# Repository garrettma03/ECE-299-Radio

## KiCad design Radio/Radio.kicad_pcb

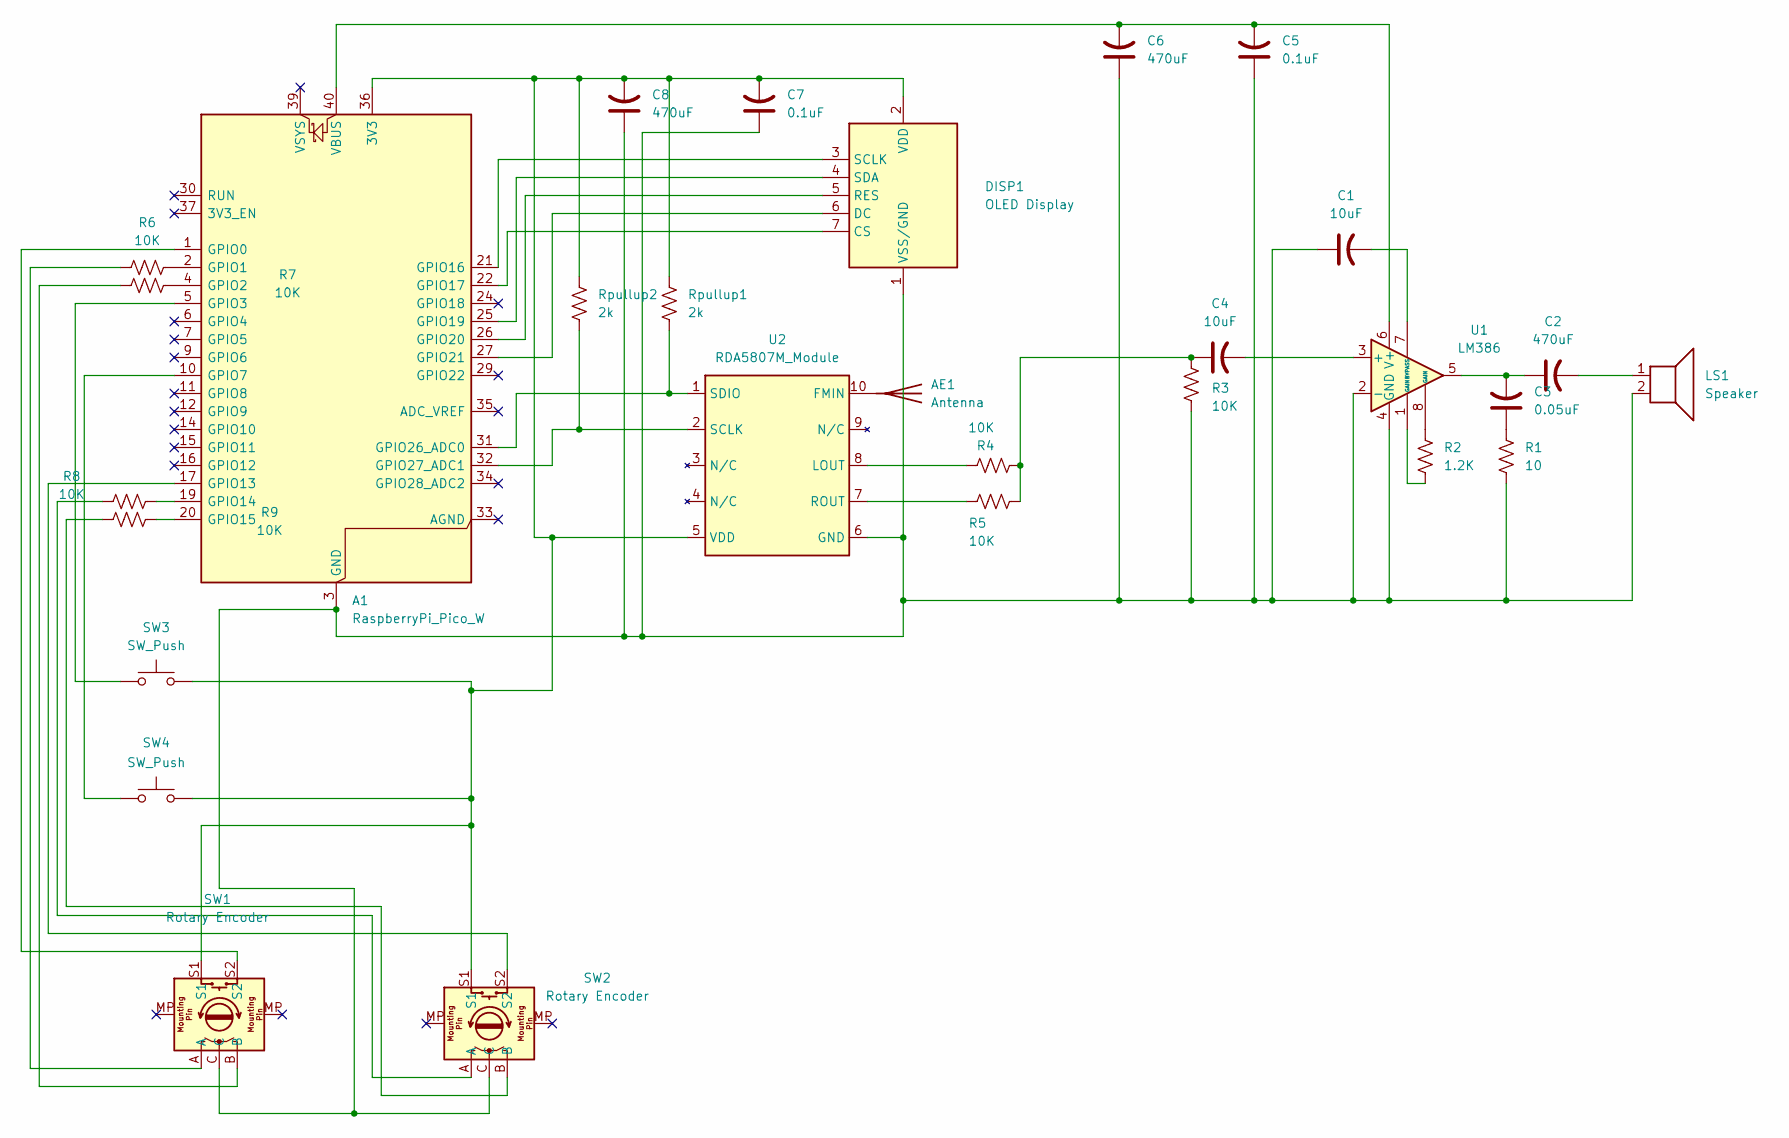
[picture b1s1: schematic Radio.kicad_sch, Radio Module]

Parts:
A1: RaspberryPi_Pico_W; RPi_Pico_TH
AE1: Antenna; TestPoint_Pad_D1.0mm
C1, C4: 10uF; CP_Radial_D6.3mm_P2.50mm
C2, C6, C8: 470uF; CP_Radial_D6.3mm_P2.50mm
C3: 0.05uF; C_Disc_D3.0mm_W1.6mm_P2.50mm
C5, C7: 0.1uF; C_Disc_D3.0mm_W1.6mm_P2.50mm
DISP1: OLED Display; OLED_Display_1.3
LS1: Speaker; TerminalBlock_Phoenix_MKDS-1,5-2_1x02_P5.00mm_Horizontal
R1: 10; R_Axial_DIN0207_L6.3mm_D2.5mm_P10.16mm_Horizontal
R2: 1.2K; R_Axial_DIN0207_L6.3mm_D2.5mm_P10.16mm_Horizontal
R3, R4, R5, R6, R7, R8, R9: 10K; R_Axial_DIN0207_L6.3mm_D2.5mm_P10.16mm_Horizontal
Rpullup1, Rpullup2: 2k; R_Axial_DIN0207_L6.3mm_D2.5mm_P10.16mm_Horizontal
SW1, SW2: Rotary Encoder; RotaryEncoder_Alps_EC12E-Switch_Vertical_H20mm
SW3, SW4: SW_Push; SW_PUSH_6mm
U1: LM386; DIP-8_W7.62mm
U2: RDA5807M_Module; RDA5807M_Module_TH

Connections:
unnamed: A1.36 (3V3), C7.2, C8.2, DISP1.2 (VDD), Rpullup1.1, Rpullup2.1, SW1.S1, SW2.S1, SW3.2, SW4.2, U2.5 (VDD)
unnamed: A1.1 (GPIO0), SW1.S2
unnamed: A1.2 (GPIO1), R6.2
unnamed: A1.4 (GPIO2), R7.2
unnamed: A1.5 (GPIO3), SW3.1
unnamed: A1.10 (GPIO7), SW4.1
unnamed: A1.17 (GPIO13), SW2.S2
unnamed: A1.19 (GPIO14), R8.2
unnamed: A1.20 (GPIO15), R9.2
unnamed: A1.21 (GPIO16), DISP1.3 (SCLK)
unnamed: A1.22 (GPIO17), DISP1.7 (CS)
unnamed: A1.25 (GPIO19), DISP1.4 (SDA)
unnamed: A1.26 (GPIO20), DISP1.5 (RES)
unnamed: A1.27 (GPIO21), DISP1.6 (DC)
unnamed: A1.31 (GPIO26_ADC0), Rpullup1.2, U2.1 (SDIO)
unnamed: A1.32 (GPIO27_ADC1), Rpullup2.2, U2.2 (SCLK)
unnamed: A1.40 (VBUS), C5.2, C6.2, U1.6 (V+)
unnamed: AE1.1 (A), U2.10 (FMIN)
unnamed: C2.1, C3.2, U1.5
unnamed: C2.2, LS1.1
unnamed: C3.1, R1.2
unnamed: C4.1, R3.2, R4.1, R5.2
unnamed: A1.3 (GND), A1.8 (GND), A1.13 (GND), A1.18 (GND), A1.23 (GND), A1.28 (GND), A1.38 (GND), C1.1, C5.1, C6.1, C7.1, C8.1, DISP1.1 (VSS/GND), LS1.2, R1.1, R3.1, SW1.C, SW2.C, U1.2 (-), U1.4 (GND), U2.6 (GND)
unnamed: R2.1, U1.1 (GAIN)
unnamed: R2.2, U1.8 (GAIN)
unnamed: R6.1, SW1.A
unnamed: R7.1, SW1.B
unnamed: R8.1, SW2.A
unnamed: R9.1, SW2.B
unnamed: C4.2, U1.3 (+)
unnamed: C1.2, U1.7 (BYPASS)
unnamed: R4.2, U2.8 (LOUT)
unnamed: R5.1, U2.7 (ROUT)

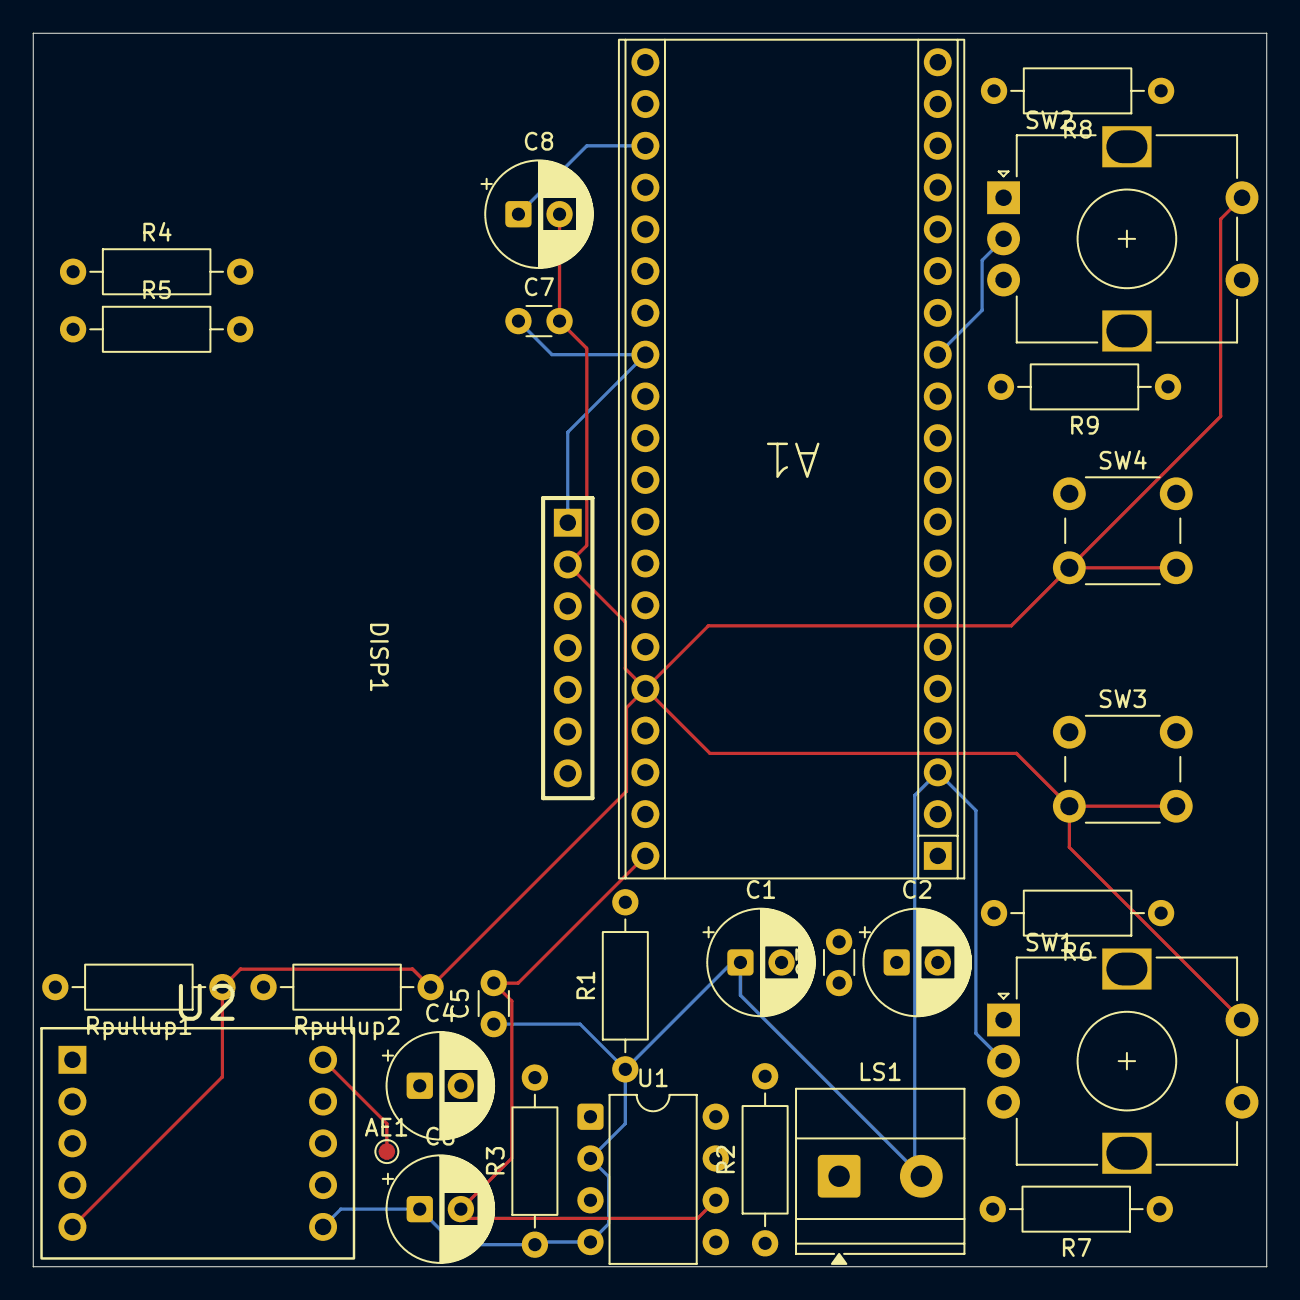
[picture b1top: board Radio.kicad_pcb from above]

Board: 4 copper layers, 75.0 x 75.0 mm, 29 parts (0 on the bottom side), 33 nets.

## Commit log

2025-06-20 Create radio.py
    Added for volume control and radio adjustment
2025-06-20 added 2 rotary encoders and 4 buttons
2025-06-21 Fixed some of schematic and added footprints. Added schematic to the PCB editor and now I got to redesign the schematic so all connections work
2025-06-23 Finished making first version of the pcb design. Added fornt and back copper and filled the back with copper. Also removed one of the two amplifiers.
2025-07-09 added test for buttons and rotary
2025-07-09 Updated Schematic
2025-07-11 updated PCB with filters
2025-07-11 added volume control
2025-07-11 Made PCB and moved a few gpio pins for buttons
2025-07-16 Added mounting holes to PCB
2025-07-18 added preliminary features for tracking time, alarm, frequency, volume. need to add display functionality
2025-07-27 added screen functionality
2025-07-28 more radio functionality added
2025-07-30 added radio functionality
2025-08-01 Added enlosure files
